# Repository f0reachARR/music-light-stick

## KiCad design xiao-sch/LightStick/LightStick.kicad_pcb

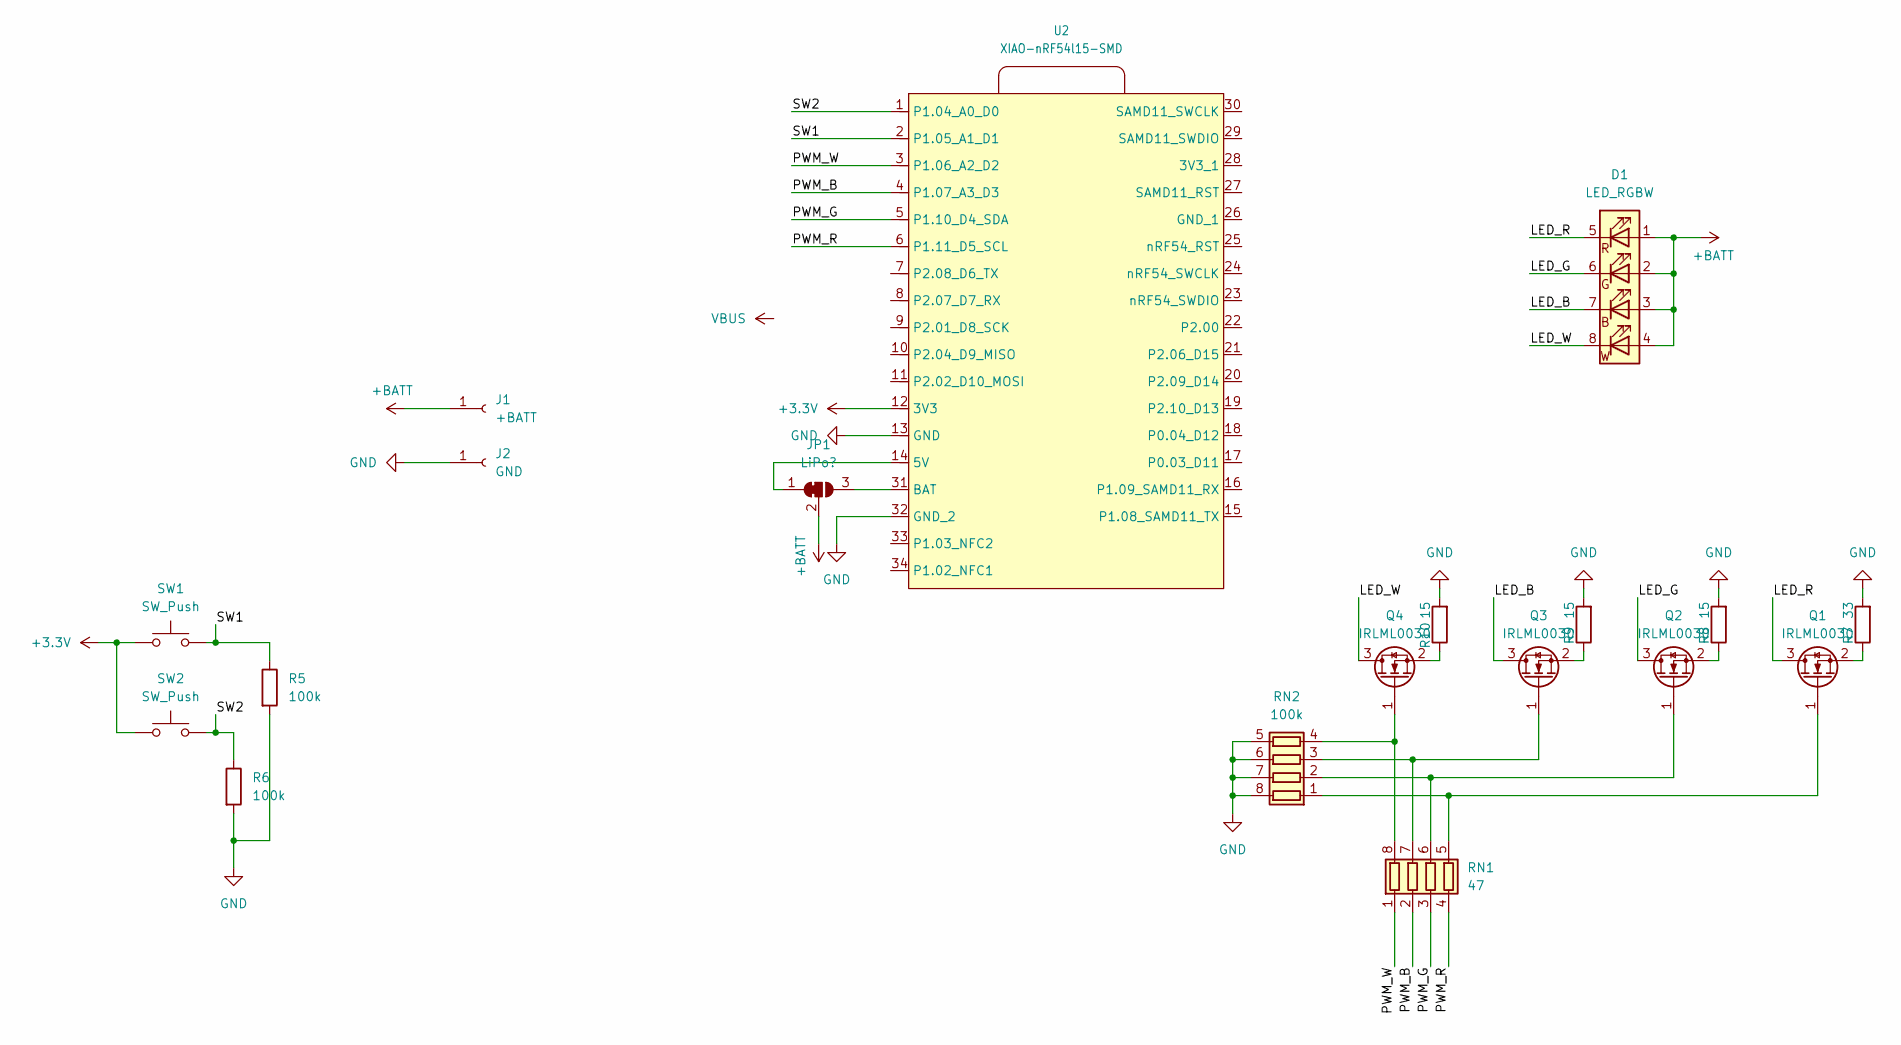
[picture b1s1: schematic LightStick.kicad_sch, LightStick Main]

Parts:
D1: LED_RGBW; XL-5050RGBW
J1: +BATT; TestPoint_Pad_D2.5mm
J2: GND; TestPoint_Pad_D2.5mm
JP1: LiPo?; SolderJumper-3_P1.3mm_Bridged12_RoundedPad1.0x1.5mm
Q1, Q2, Q3, Q4: IRLML0030; SOT-23
R5, R6: 100k; R_0603_1608Metric_Pad0.98x0.95mm_HandSolder
R7: 33; R_0603_1608Metric_Pad0.98x0.95mm_HandSolder
R8, R9, R10: 15; R_0603_1608Metric_Pad0.98x0.95mm_HandSolder
RN1: 47; R_Array_Concave_4x0603
RN2: 100k; R_Array_Concave_4x0603
SW1, SW2: SW_Push; SW_SPST_PTS647_Sx38
U2: XIAO-nRF54l15-SMD

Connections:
+3.3V: SW1.1, SW2.1, U2.12 (3V3)
+BATT: D1.1 (RA), D1.2 (GA), D1.3 (BA), D1.4 (WA), J1.1, JP1.2 (C)
/LED_B: D1.7 (BK), Q3.3 (D)
/LED_G: D1.6 (GK), Q2.3 (D)
/LED_R: D1.5 (RK), Q1.3 (D)
/LED_W: D1.8 (WK), Q4.3 (D)
/PWM_B: RN1.2 (R2.1), U2.4 (P1.07_A3_D3)
/PWM_G: RN1.3 (R3.1), U2.5 (P1.10_D4_SDA)
/PWM_R: RN1.4 (R4.1), U2.6 (P1.11_D5_SCL)
/PWM_W: RN1.1 (R1.1), U2.3 (P1.06_A2_D2)
/SW1: R5.1, SW1.2, U2.2 (P1.05_A1_D1)
/SW2: R6.1, SW2.2, U2.1 (P1.04_A0_D0)
GND: J2.1, R5.2, R6.2, R7.2, R8.2, R9.2, R10.2, RN2.5 (R4.2), RN2.6 (R3.2), RN2.7 (R2.2), RN2.8 (R1.2), U2.13 (GND), U2.32 (GND_2)
unnamed: JP1.1 (A), U2.14 (5V)
unnamed: JP1.3 (B), U2.31 (BAT)
unnamed: Q1.1 (G), RN1.5 (R4.2), RN2.1 (R1.1)
unnamed: Q1.2 (S), R7.1
unnamed: Q2.1 (G), RN1.6 (R3.2), RN2.2 (R2.1)
unnamed: Q2.2 (S), R8.1
unnamed: Q3.1 (G), RN1.7 (R2.2), RN2.3 (R3.1)
unnamed: Q3.2 (S), R9.1
unnamed: Q4.1 (G), RN1.8 (R1.2), RN2.4 (R4.1)
unnamed: Q4.2 (S), R10.1

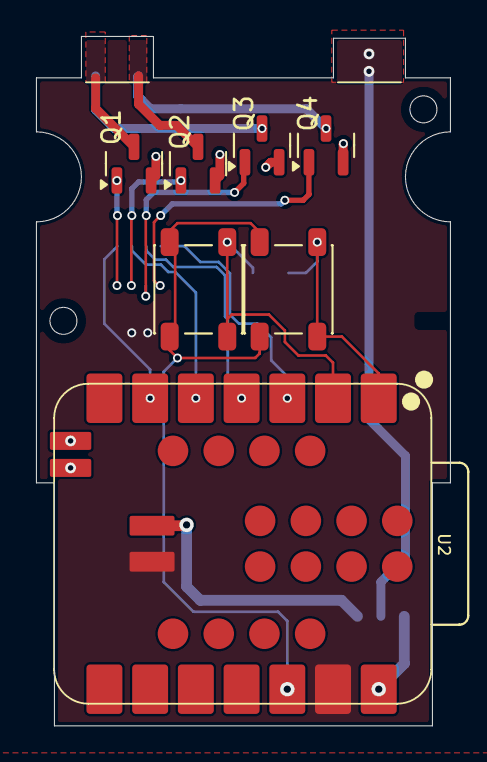
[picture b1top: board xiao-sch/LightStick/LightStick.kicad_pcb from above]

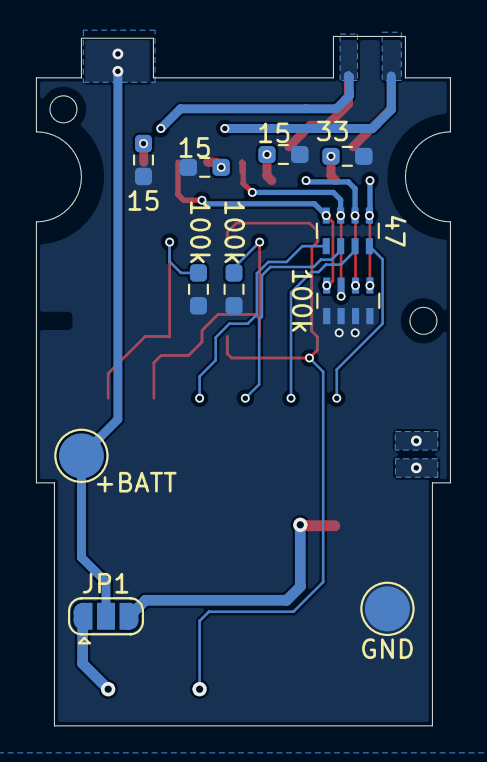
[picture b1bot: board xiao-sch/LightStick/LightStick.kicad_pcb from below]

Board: 2 copper layers, 23.0 x 38.3 mm, 18 parts (11 on the bottom side), 19 nets.

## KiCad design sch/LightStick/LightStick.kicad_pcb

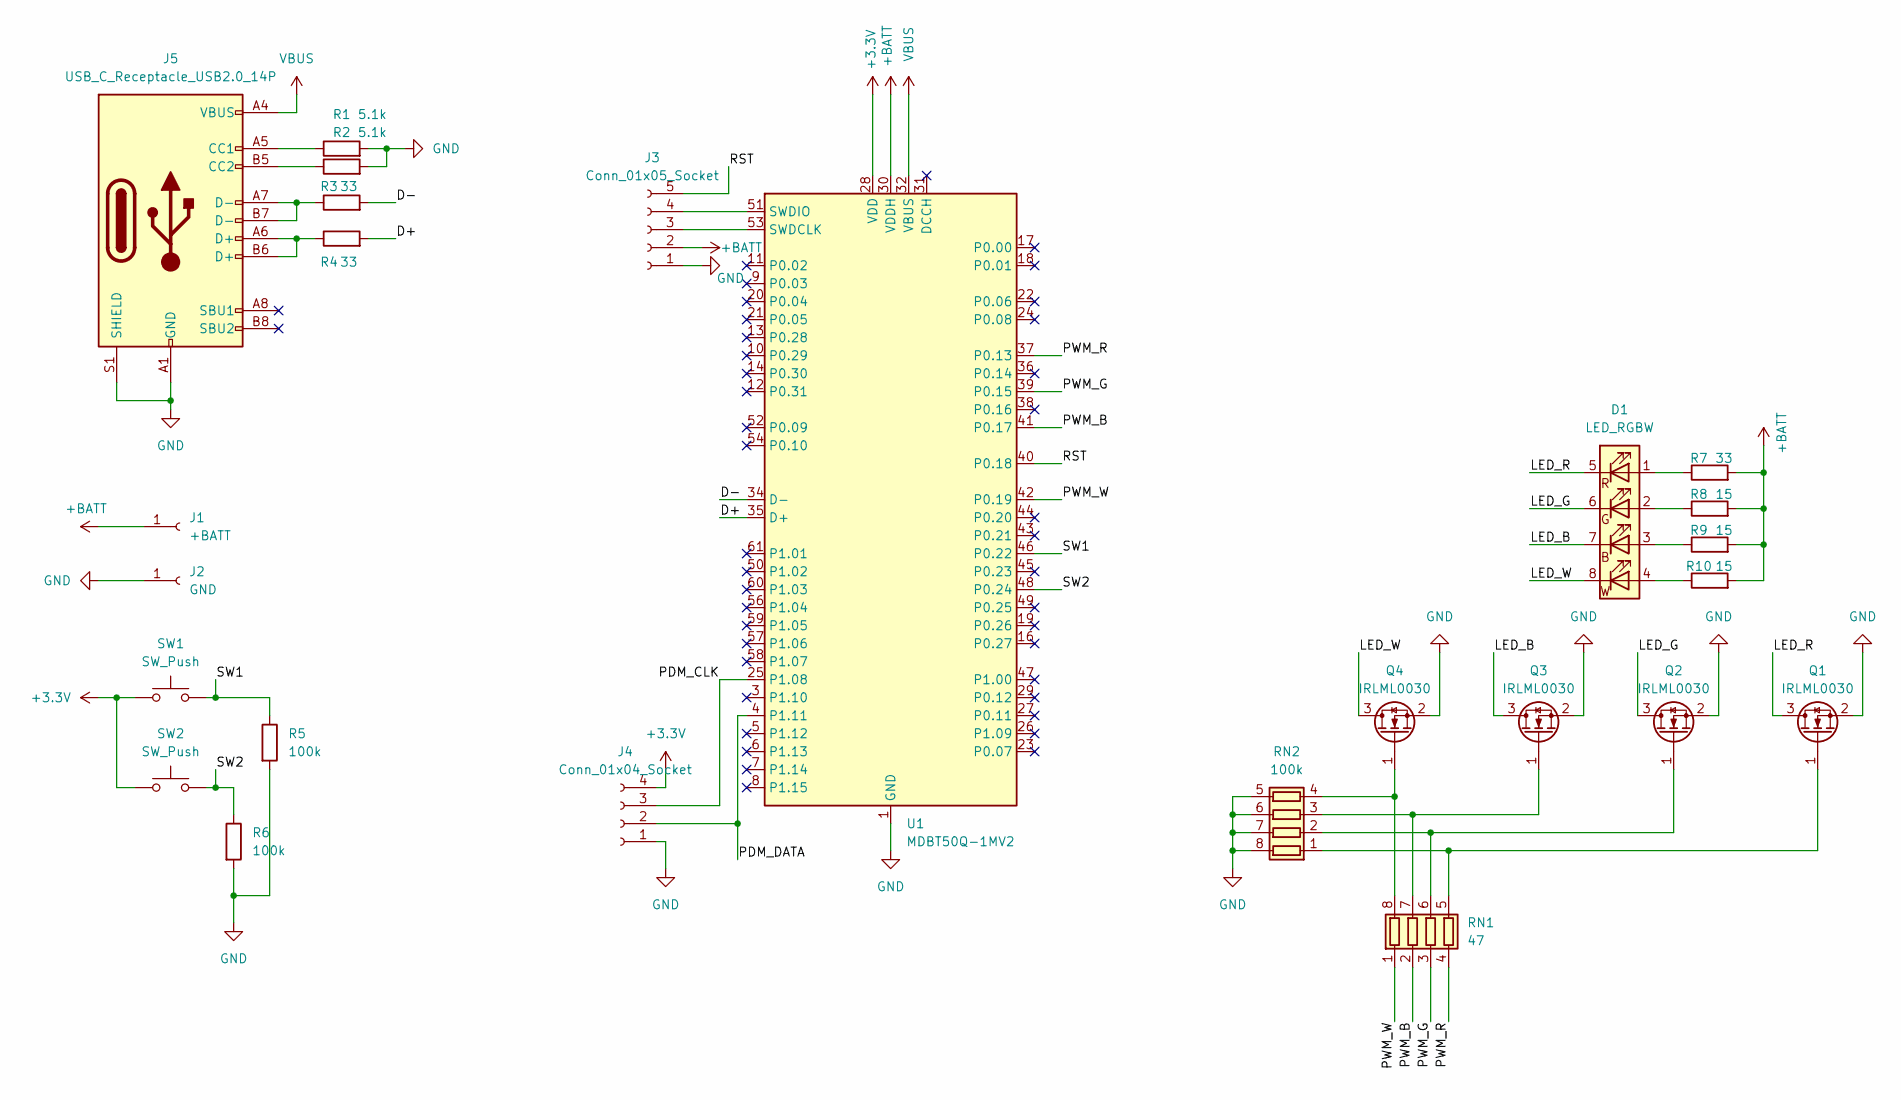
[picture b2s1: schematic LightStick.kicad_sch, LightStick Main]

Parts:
D1: LED_RGBW; XL-5050RGBW
J1: +BATT; TestPoint_Pad_D2.5mm
J2: GND; TestPoint_Pad_D2.5mm
J3: Conn_01x05_Socket; JST_SH_SM05B-SRSS-TB_1x05-1MP_P1.00mm_Horizontal
J4: Conn_01x04_Socket; JST_SH_SM04B-SRSS-TB_1x04-1MP_P1.00mm_Horizontal
J5: USB_C_Receptacle_USB2.0_14P; USB_C_Receptacle_Palconn_UTC16-G
Q1, Q2, Q3, Q4: IRLML0030; SOT-23
R1, R2: 5.1k; R_0603_1608Metric_Pad0.98x0.95mm_HandSolder
R3, R4, R7: 33; R_0603_1608Metric_Pad0.98x0.95mm_HandSolder
R5, R6: 100k; R_0603_1608Metric_Pad0.98x0.95mm_HandSolder
R8, R9, R10: 15; R_0603_1608Metric_Pad0.98x0.95mm_HandSolder
RN1: 47; R_Array_Concave_4x0603
RN2: 100k; R_Array_Concave_4x0603
SW1, SW2: SW_Push; SW_SPST_PTS647_Sx38
U1: MDBT50Q-1MV2; Raytac_MDBT50Q

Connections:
+3.3V: J4.4, SW1.1, SW2.1, U1.28 (VDD)
+BATT: J1.1, J3.2, R7.2, R8.2, R9.2, R10.2, U1.30 (VDDH)
/D+: R4.2, U1.35 (D+)
/D-: R3.2, U1.34 (D-)
/LED_B: D1.7 (BK), Q3.3 (D)
/LED_G: D1.6 (GK), Q2.3 (D)
/LED_R: D1.5 (RK), Q1.3 (D)
/LED_W: D1.8 (WK), Q4.3 (D)
/PDM_CLK: J4.3, U1.25 (P1.08)
/PDM_DATA: J4.2, U1.4 (P1.11)
/PWM_B: RN1.2 (R2.1), U1.41 (P0.17)
/PWM_G: RN1.3 (R3.1), U1.39 (P0.15)
/PWM_R: RN1.4 (R4.1), U1.37 (P0.13)
/PWM_W: RN1.1 (R1.1), U1.42 (P0.19)
/RST: J3.5, U1.40 (P0.18)
/SW1: R5.1, SW1.2, U1.46 (P0.22)
/SW2: R6.1, SW2.2, U1.48 (P0.24)
GND: J2.1, J3.1, J4.1, J5.A1 (GND), J5.A12 (GND), J5.B1 (GND), J5.B12 (GND), J5.S1 (SHIELD), Q1.2 (S), Q2.2 (S), Q3.2 (S), Q4.2 (S), R1.2, R2.2, R5.2, R6.2, RN2.5 (R4.2), RN2.6 (R3.2), RN2.7 (R2.2), RN2.8 (R1.2), U1.1 (GND), U1.2 (GND), U1.15 (GND), U1.33 (GND), U1.55 (GND)
unnamed: D1.3 (BA), R9.1
unnamed: D1.2 (GA), R8.1
unnamed: D1.1 (RA), R7.1
unnamed: D1.4 (WA), R10.1
unnamed: J3.3, U1.53 (SWDCLK)
unnamed: J3.4, U1.51 (SWDIO)
unnamed: J5.A5 (CC1), R1.1
unnamed: J5.B5 (CC2), R2.1
unnamed: J5.A6 (D+), J5.B6 (D+), R4.1
unnamed: J5.A7 (D-), J5.B7 (D-), R3.1
unnamed: Q1.1 (G), RN1.5 (R4.2), RN2.1 (R1.1)
unnamed: Q2.1 (G), RN1.6 (R3.2), RN2.2 (R2.1)
unnamed: Q3.1 (G), RN1.7 (R2.2), RN2.3 (R3.1)
unnamed: Q4.1 (G), RN1.8 (R1.2), RN2.4 (R4.1)
VBUS: J5.A4 (VBUS), J5.A9 (VBUS), J5.B4 (VBUS), J5.B9 (VBUS), U1.32 (VBUS)

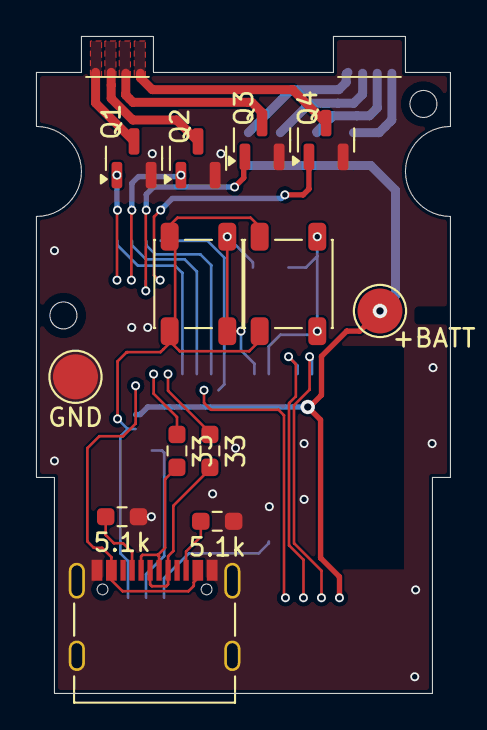
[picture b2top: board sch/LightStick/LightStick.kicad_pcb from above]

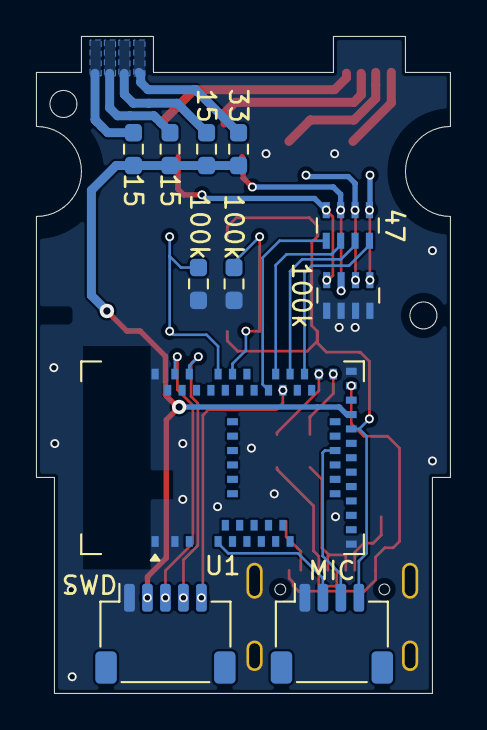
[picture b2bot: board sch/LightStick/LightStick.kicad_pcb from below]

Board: 2 copper layers, 23.0 x 36.5 mm, 24 parts (11 on the bottom side), 25 nets.

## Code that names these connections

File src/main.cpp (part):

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LOG_MODULE_REGISTER(penlight, LOG_LEVEL_DBG);

// Device tree aliases for PWM LEDs
static const struct pwm_dt_spec pwm_r = PWM_DT_SPEC_GET(DT_ALIAS(pwm_led_r));
static const struct pwm_dt_spec pwm_g = PWM_DT_SPEC_GET(DT_ALIAS(pwm_led_g));
static const struct pwm_dt_spec pwm_b = PWM_DT_SPEC_GET(DT_ALIAS(pwm_led_b));
static const struct pwm_dt_spec pwm_w = PWM_DT_SPEC_GET(DT_ALIAS(pwm_led_w));

// Device tree specs for buttons
static const struct gpio_dt_spec button_next_spec = GPIO_DT_SPEC_GET(DT_ALIAS(button0), gpios);
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
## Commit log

2025-10-04 Bootable
2025-10-06 Works but not precise
2025-10-11 Add XIAO based board
2025-10-12 Raytac Module version
2025-10-14 Add some BLE implementation
2025-10-22 Add settings
2025-10-25 support additional mode
2025-10-25 Dual button
2025-10-25 Add deep sleep feature
2025-10-26 Settings Fix
2026-02-07 xiao wip
2026-02-07 remove spec
2026-02-07 remove cpp
2026-02-08 rewrite with c

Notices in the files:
src/main.cpp:
SPDX-License-Identifier: Apache-2.0
